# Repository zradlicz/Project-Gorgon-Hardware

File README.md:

# SDI-12 Underground Temperature Sensor

A 7-channel 4-wire RTD temperature measurement device that communicates via the SDI-12 protocol, designed for underground temperature profiling applications.

## Overview

This device is an SDI-12 sensor that provides high-precision temperature measurements from seven 4-wire RTD (Resistance Temperature Detector) inputs. It is designed for underground temperature sensing applications such as soil temperature profiling, permafrost monitoring, and geothermal studies. The 4-wire RTD configuration eliminates lead resistance errors, enabling accurate measurements even with long cable runs to buried sensors.

Built around the Raspberry Pi RP2040 microcontroller and featuring a 24-bit ADC, the sensor integrates seamlessly with existing SDI-12 data logger infrastructure.

## Features

- **7 channels** of 4-wire RTD temperature measurement
- **24-bit precision ADC** (AD7124-8) for high-resolution measurements
- **8-channel analog multiplexer** (ADG708) for RTD channel selection
- **SDI-12 protocol** compatible with standard environmental data loggers
- **RP2040 microcontroller** (dual-core Arm Cortex-M0+)
- **USB interface** for configuration and direct data access
- **128Mb flash memory** for configuration storage
- **Weatherproof enclosure** with gasket seal for field deployment

## Hardware Specifications

| Parameter | Value |
|-----------|-------|
| RTD Channels | 7 (4-wire configuration) |
| ADC Resolution | 24-bit |
| Communication | SDI-12, USB |
| Power Supply | 5V |
| Logic Level | 3.3V (internal) |
| MCU | RP2040 (Raspberry Pi) |

## Key Components

| Reference | Part | Description |
|-----------|------|-------------|
| U7 | RP2040 | Main microcontroller |
| U8 | AD7124-8BCPZ | 24-bit 8-channel ADC |
| U5 | ADG708BRUZ | 8-channel analog multiplexer |
| U4 | W25Q128JVS | 128Mb SPI flash memory |
| U3 | TXS0102DCT | Bidirectional level shifter |
| U2 | NCP1117-3.3 | 3.3V voltage regulator |
| U1 | LP2950-5.0 | 5V voltage regulator |

## Repository Structure

```
├── sdi12-analog-mux.kicad_sch    # KiCad schematic
├── sdi12-analog-mux.kicad_pcb    # KiCad PCB layout
├── sdi12-analog-mux.kicad_pro    # KiCad project file
├── sdi12-analog-mux.step         # 3D model of assembled PCB
├── CAD/
│   ├── assembly.FCStd            # FreeCAD full assembly
│   ├── bottom_housing.FCStd      # Bottom enclosure design
│   ├── PCB.FCStd                 # PCB model
│   └── enclosure/
│       ├── Bottom.stl            # 3D printable bottom housing
│       ├── Cover.stl             # 3D printable top cover
│       ├── Gasket.stl            # 3D printable gasket
│       ├── Gasket_Drawing.dxf    # Gasket cutting template
│       └── *.step                # STEP files for CAD import
└── production/
    ├── bom.csv                   # Bill of materials
    ├── positions.csv             # Component placement data
    ├── designators.csv           # Component designators
    └── netlist.ipc               # IPC netlist
```

## Applications

- Soil temperature profiling
- Permafrost and active layer monitoring
- Geothermal gradient measurement
- Agricultural soil monitoring
- Infrastructure temperature monitoring (roads, pipelines)
- Environmental research

## Manufacturing

Production files are located in the `production/` directory:
- **BOM**: `bom.csv` contains the complete bill of materials
- **Pick and Place**: `positions.csv` provides component placement coordinates
- **Gerbers**: Included in `sdi12-analog-mux.zip`

## Enclosure

The enclosure is designed for 3D printing and field deployment:
- Bottom housing with mounting features
- Top cover
- Gasket for weatherproof sealing
- Provisions for cable glands and ventilation

STL files for printing and STEP files for CAD integration are provided in `CAD/enclosure/`.

## Design Tools

- **PCB Design**: KiCad 8
- **Mechanical Design**: FreeCAD

## License

This project is open-source hardware.

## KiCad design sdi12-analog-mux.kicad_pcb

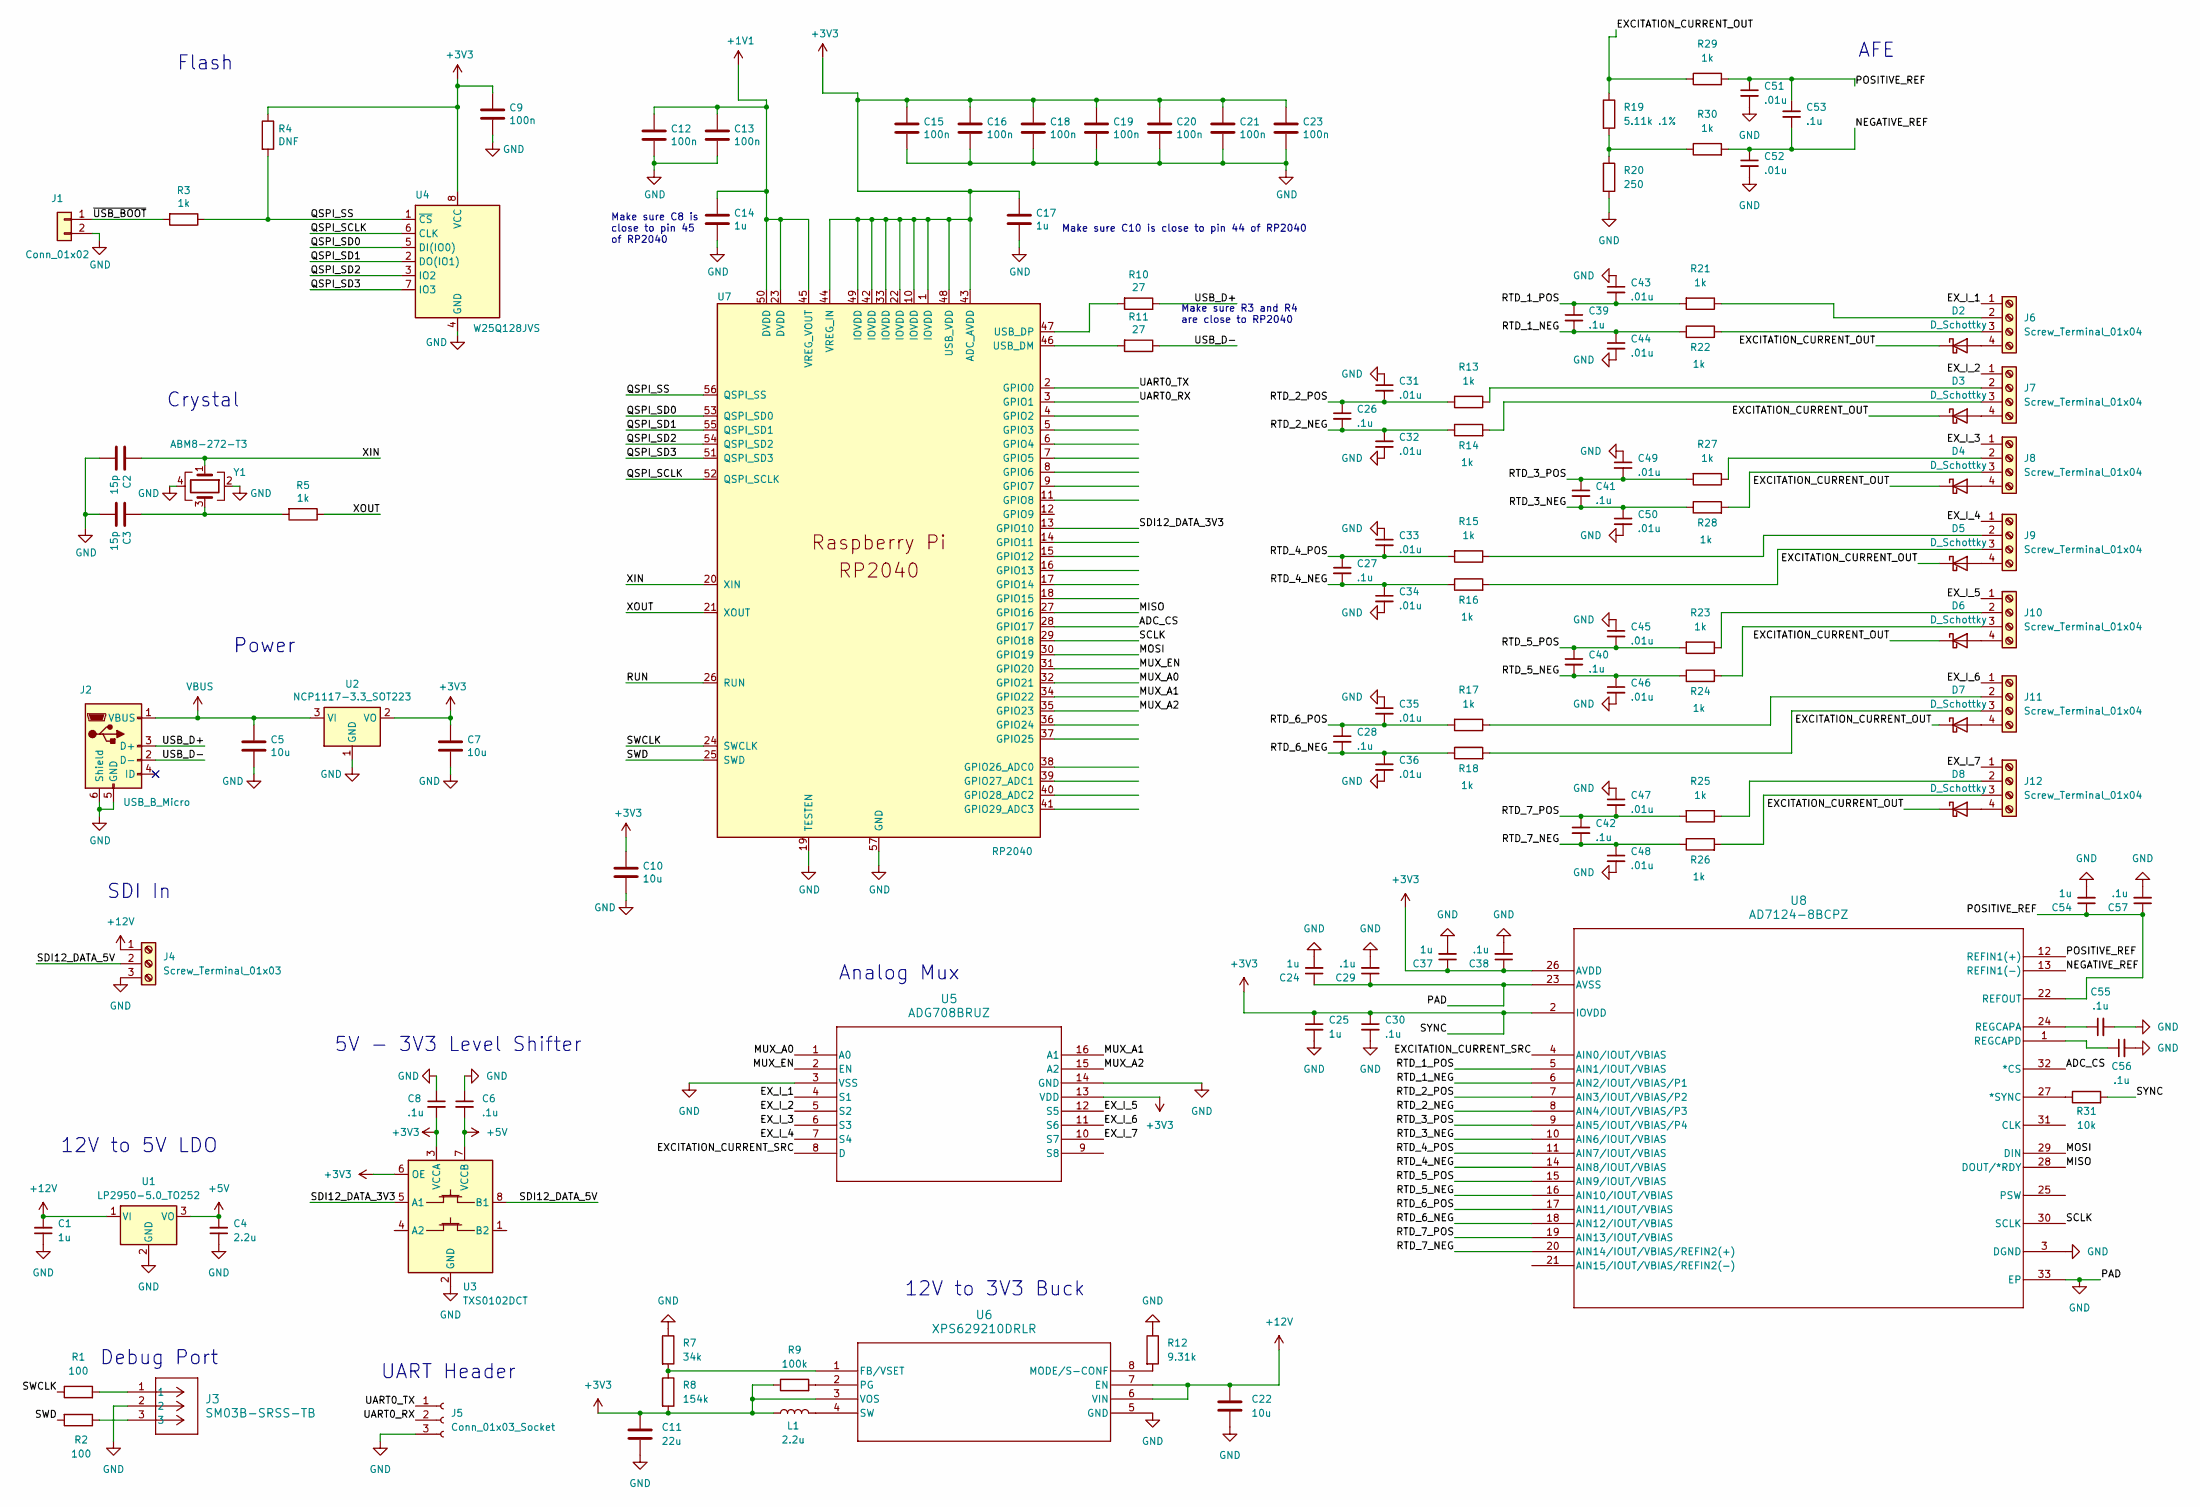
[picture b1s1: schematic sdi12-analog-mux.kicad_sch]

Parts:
C1, C24, C25, C37: 1u; C_0805_2012Metric
C2, C3: 15p; C_0402_1005Metric
C4: 2.2u; C_0402_1005Metric
C5, C7, C10: 10u; C_0805_2012Metric
C6, C8, C26, C27, C28, C29, C30, C38, C39, C40, C41, C42, C53, C55, C56, C57: .1u; C_0402_1005Metric
C9, C12, C13, C15, C16, C18, C19, C20, C21, C23: 100n; C_0402_1005Metric
C11: 22u; C_0402_1005Metric
C14, C17, C54: 1u; C_0402_1005Metric
C22: 10u; C_0402_1005Metric
C31, C32, C33, C34, C35, C36, C43, C44, C45, C46, C47, C48, C49, C50, C51, C52: .01u; C_0402_1005Metric
D2, D3, D4, D5, D6, D7, D8: D_Schottky; D_SOD-323F
J1: Conn_01x02; PinHeader_1x02_P2.54mm_Vertical
J2: USB_B_Micro; USB_Micro-B_Amphenol_10103594-0001LF_Horizontal_modified
J3: SM03B-SRSS-TB; CONN_SM03B-SRSS-TB_JST
J4: Screw_Terminal_01x03; TerminalBlock_Xinya_XY308-2.54-3P_1x03_P2.54mm_Horizontal
J5: Conn_01x03_Socket; PinHeader_1x03_P2.54mm_Vertical
J6, J7, J8, J9, J10, J11, J12: Screw_Terminal_01x04; TerminalBlock_Xinya_XY308-2.54-4P_1x04_P2.54mm_Horizontal
L1: 2.2u; WE-MAPI_3012
R1, R2: 100; R_0402_1005Metric
R3, R5, R13, R14, R15, R16, R17, R18, R21, R22, R23, R24, R25, R26, R27, R28, R29, R30: 1k; R_0402_1005Metric
R4: DNF; R_0402_1005Metric
R7: 34k; R_0402_1005Metric
R8: 154k; R_0402_1005Metric
R9: 100k; R_0402_1005Metric
R10, R11: 27; R_0402_1005Metric
R12: 9.31k; R_0402_1005Metric
R19: 5.11k .1%; R_0402_1005Metric
R20: 250; R_0402_1005Metric
R31: 10k; R_0402_1005Metric
U1: LP2950-5.0_TO252; TO-252-2
U2: NCP1117-3.3_SOT223; SOT-223-3_TabPin2
U3: TXS0102DCT; SSOP-8_2.95x2.8mm_P0.65mm
U4: W25Q128JVS; SOIC-8_5.23x5.23mm_P1.27mm
U5: ADG708BRUZ; RU_16_ADI
U6: XPS629210DRLR; SOT_9210DRLR_TEX-M
U7: RP2040; RP2040-QFN-56
U8: AD7124-8BCPZ; CP_32_12_ADI-M
Y1: ABM8-272-T3; Crystal_SMD_3225-4Pin_3.2x2.5mm

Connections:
+1V1: C12.1, C13.1, C14.1, U7.23 (DVDD), U7.45 (VREG_VOUT), U7.50 (DVDD)
+3V3: C7.1, C8.2, C9.1, C10.1, C11.1, C15.1, C16.1, C17.1, C18.1, C19.1, C20.1, C21.1, C23.1, C25.1, C30.1, C37.1, C38.1, L1.1, R4.1, R8.2, R9.1, R31.2, U2.2 (VO), U3.3 (VCCA), U3.6 (OE), U4.8 (VCC), U5.13 (VDD), U6.3 (VOS), U7.1 (IOVDD), U7.10 (IOVDD), U7.22 (IOVDD), U7.33 (IOVDD), U7.42 (IOVDD), U7.43 (ADC_AVDD), U7.44 (VREG_IN), U7.48 (USB_VDD), U7.49 (IOVDD), U8.2 (IOVDD), U8.26 (AVDD)
+5V: C4.2, C6.2, U1.3 (VO), U3.7 (VCCB)
+12V: C1.2, C22.1, J4.1, U1.1 (VI), U6.6 (VIN), U6.7 (EN)
/ADC_CS: U7.28 (GPIO17), U8.32 (*CS)
/EXCITATION_CURRENT_OUT: D2.1 (K), D3.1 (K), D4.1 (K), D5.1 (K), D6.1 (K), D7.1 (K), D8.1 (K), R19.1, R29.1
/EXCITATION_CURRENT_SRC: U5.8 (D), U8.4 (AIN0/IOUT/VBIAS)
/EX_I_1: J6.1, U5.4 (S1)
/EX_I_2: J7.1, U5.5 (S2)
/EX_I_3: J8.1, U5.6 (S3)
/EX_I_4: J9.1, U5.7 (S4)
/EX_I_5: J10.1, U5.12 (S5)
/EX_I_6: J11.1, U5.11 (S6)
/EX_I_7: J12.1, U5.10 (S7)
/MISO: U7.27 (GPIO16), U8.28 (DOUT/*RDY)
/MOSI: U7.30 (GPIO19), U8.29 (DIN)
/MUX_A0: U5.1 (A0), U7.32 (GPIO21)
/MUX_A1: U5.16 (A1), U7.34 (GPIO22)
/MUX_A2: U5.15 (A2), U7.35 (GPIO23)
/MUX_EN: U5.2 (EN), U7.31 (GPIO20)
/NEGATIVE_REF: C52.1, C53.2, R30.2, U8.13 (REFIN1(-))
/POSITIVE_REF: C51.1, C53.1, C54.1, C57.1, R29.2, U8.12 (REFIN1(+)), U8.22 (REFOUT)
/QSPI_SCLK: U4.6 (CLK), U7.52 (QSPI_SCLK)
/QSPI_SD0: U4.5 (DI(IO0)), U7.53 (QSPI_SD0)
/QSPI_SD1: U4.2 (DO(IO1)), U7.55 (QSPI_SD1)
/QSPI_SD2: U4.3 (IO2), U7.54 (QSPI_SD2)
/QSPI_SD3: U4.7 (IO3), U7.51 (QSPI_SD3)
/QSPI_SS: R3.1, R4.2, U4.1 (~CS), U7.56 (QSPI_SS)
/RTD_1_NEG: C39.2, C44.1, R22.1, U8.6 (AIN2/IOUT/VBIAS/P1)
/RTD_1_POS: C39.1, C43.2, R21.2, U8.5 (AIN1/IOUT/VBIAS)
/RTD_2_NEG: C26.2, C32.1, R14.1, U8.8 (AIN4/IOUT/VBIAS/P3)
/RTD_2_POS: C26.1, C31.2, R13.2, U8.7 (AIN3/IOUT/VBIAS/P2)
/RTD_3_NEG: C41.2, C50.1, R28.1, U8.10 (AIN6/IOUT/VBIAS)
/RTD_3_POS: C41.1, C49.2, R27.2, U8.9 (AIN5/IOUT/VBIAS/P4)
/RTD_4_NEG: C27.2, C34.1, R16.1, U8.14 (AIN8/IOUT/VBIAS)
/RTD_4_POS: C27.1, C33.2, R15.2, U8.11 (AIN7/IOUT/VBIAS)
/RTD_5_NEG: C40.2, C46.1, R24.1, U8.16 (AIN10/IOUT/VBIAS)
/RTD_5_POS: C40.1, C45.2, R23.2, U8.15 (AIN9/IOUT/VBIAS)
/RTD_6_NEG: C28.2, C36.1, R18.1, U8.18 (AIN12/IOUT/VBIAS)
/RTD_6_POS: C28.1, C35.2, R17.2, U8.17 (AIN11/IOUT/VBIAS)
/RTD_7_NEG: C42.2, C48.1, R26.1, U8.20 (AIN14/IOUT/VBIAS/REFIN2(+))
/RTD_7_POS: C42.1, C47.2, R25.2, U8.19 (AIN13/IOUT/VBIAS)
/RUN: U7.26 (RUN)
/SCLK: U7.29 (GPIO18), U8.30 (SCLK)
/SDI12_DATA_3V3: U3.5 (A1), U7.13 (GPIO10)
/SDI12_DATA_5V: J4.2, U3.8 (B1)
/SWCLK: R1.1, U7.24 (SWCLK)
/SWD: R2.2, U7.25 (SWD)
/UART0_RX: J5.2, U7.3 (GPIO1)
/UART0_TX: J5.1, U7.2 (GPIO0)
/USB_D+: J2.3 (D+), R10.1
/USB_D-: J2.2 (D-), R11.1
/XIN: C2.1, U7.20 (XIN), Y1.1
/XOUT: R5.1, U7.21 (XOUT)
/~USB_BOOT: J1.1, R3.2
GND: C1.1, C2.2, C3.2, C4.1, C5.2, C6.1, C7.2, C8.1, C9.2, C10.2, C11.2, C12.2, C13.2, C14.2, C15.2, C16.2, C17.2, C18.2, C19.2, C20.2, C21.2, C22.2, C23.2, C24.1, C24.2, C25.2, C29.1, C29.2, C30.2, C31.1, C32.2, C33.1, C34.2, C35.1, C36.2, C37.2, C38.2, C43.1, C44.2, C45.1, C46.2, C47.1, C48.2, C49.1, C50.2, C51.2, C52.2, C54.2, C55.2, C56.2, C57.2, J1.2, J2.5 (GND), J2.6 (Shield), J3.2, J4.3, J5.3, R7.1, R12.1, R20.2, U1.2 (GND), U2.1 (GND), U3.2 (GND), U4.4 (GND), U5.3 (VSS), U5.14 (GND), U6.5 (GND), U7.19 (TESTEN), U7.57 (GND), U8.3 (DGND), U8.23 (AVSS), U8.33 (EP), Y1.2, Y1.4
unnamed: C3.1, R5.2, Y1.3
unnamed: D2.2 (A), J6.4
unnamed: D3.2 (A), J7.4
unnamed: D4.2 (A), J8.4
unnamed: D5.2 (A), J9.4
unnamed: D6.2 (A), J10.4
unnamed: D7.2 (A), J11.4
unnamed: D8.2 (A), J12.4
unnamed: J3.1, R1.2
unnamed: J3.3, R2.1
unnamed: J6.2, R21.1
unnamed: J6.3, R22.2
unnamed: J7.2, R13.1
unnamed: J7.3, R14.2
unnamed: J8.2, R27.1
unnamed: J8.3, R28.2
unnamed: J9.2, R15.1
unnamed: J9.3, R16.2
unnamed: J10.2, R23.1
unnamed: J10.3, R24.2
unnamed: J11.2, R17.1
unnamed: J11.3, R18.2
unnamed: J12.2, R25.1
unnamed: J12.3, R26.2
unnamed: R19.2, R20.1, R30.1
unnamed: R7.2, R8.1, U6.1 (FB/VSET)
unnamed: R12.2, U6.8 (MODE/S-CONF)
unnamed: R9.2, U6.2 (PG)
unnamed: L1.2, U6.4 (SW)
unnamed: R11.2, U7.46 (USB_DM)
unnamed: R10.2, U7.47 (USB_DP)
unnamed: R31.1, U8.27 (*SYNC)
unnamed: C55.1, U8.24 (REGCAPA)
unnamed: C56.1, U8.1 (REGCAPD)
VBUS: C5.1, J2.1 (VBUS), U2.3 (VI)

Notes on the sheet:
UART Header
Power
12V to 3V3 Buck
Debug Port
5V - 3V3 Level Shifter
Crystal
Analog Mux
Flash
Make sure R3 and R4 are close to RP2040
Make sure C10 is close to pin 44 of RP2040
12V to 5V LDO
Make sure C8 is close to pin 45 of RP2040
SDI In
AFE

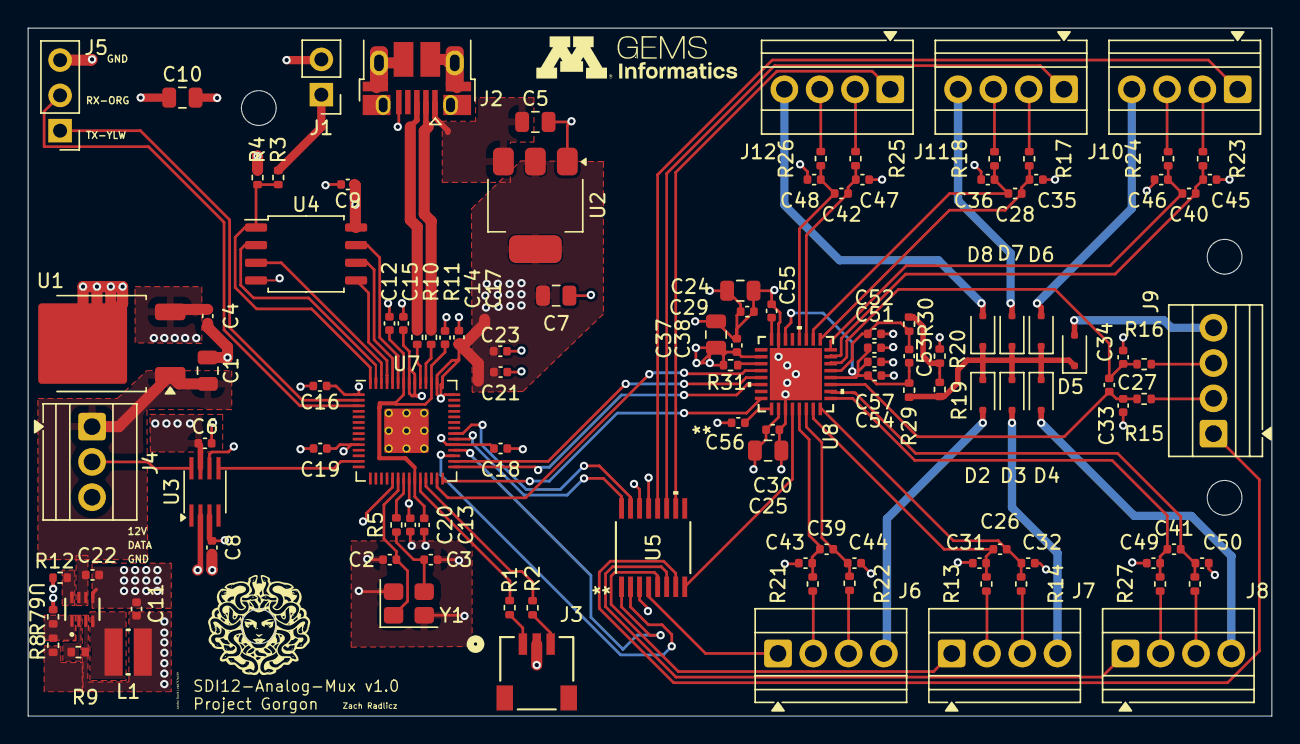
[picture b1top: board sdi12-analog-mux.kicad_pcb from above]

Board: 4 copper layers, 89.5 x 49.5 mm, 118 parts (0 on the bottom side), 90 nets.

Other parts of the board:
a: LOGO
a#2: LOGO

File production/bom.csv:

Designator,Footprint,Quantity,Value,LCSC Part #
"C1, C24, C25, C37",0805,4,1u,
"C10, C5, C7",0805,3,10u,
C11,0402,1,22u,
"C12, C13, C15, C16, C18, C19, C20, C21, C23, C9",0402,10,100n,
"C14, C17, C54",0402,3,1u,
"C2, C3",0402,2,15p,
C22,0402,1,10u,
"C26, C27, C28, C29, C30, C38, C39, C40, C41, C42, C53, C55, C56, C57, C6, C8",0402,16,.1u,
"C31, C32, C33, C34, C35, C36, C43, C44, C45, C46, C47, C48, C49, C50, C51, C52",0402,16,.01u,
C4,0402,1,2.2u,
"D2, D3, D4, D5, D6, D7, D8",D_SOD-323F,7,D_Schottky,
J1,PinHeader_1x02_P2.54mm_Vertical,1,Conn_01x02,
"J10, J11, J12, J6, J7, J8, J9",TerminalBlock_Xinya_XY308-2.54-4P_1x04_P2.54mm_Horizontal,7,Screw_Terminal_01x04,
J2,USB_Micro-B_Amphenol_10103594-0001LF_Horizontal_modified,1,USB_B_Micro,
J3,CONN_SM03B-SRSS-TB_JST,1,SM03B-SRSS-TB,
J4,TerminalBlock_Xinya_XY308-2.54-3P_1x03_P2.54mm_Horizontal,1,Screw_Terminal_01x03,
J5,PinHeader_1x03_P2.54mm_Vertical,1,Conn_01x03_Socket,
L1,WE-MAPI_3012,1,2.2u,
"R1, R2",0402,2,100,
"R10, R11",0402,2,27,
R12,0402,1,9.31k,
"R13, R14, R15, R16, R17, R18, R21, R22, R23, R24, R25, R26, R27, R28, R29, R3, R30, R5",0402,18,1k,
R19,0402,1,5.11k .1%,
R20,0402,1,250,
R31,0402,1,10k,
R4,0402,1,DNF,
R7,0402,1,34k,
R8,0402,1,154k,
R9,0402,1,100k,
U1,TO-252-2,1,LP2950-5.0_TO252,
U2,SOT-223-3_TabPin2,1,NCP1117-3.3_SOT223,
U3,SSOP-8_2.95x2.8mm_P0.65mm,1,TXS0102DCT,
U4,SOIC-8_5.23x5.23mm_P1.27mm,1,W25Q128JVS,
U5,RU_16_ADI,1,ADG708BRUZ,
U6,SOT_9210DRLR_TEX-M,1,XPS629210DRLR,
U7,RP2040-QFN-56,1,RP2040,
U8,CP_32_12_ADI-M,1,AD7124-8BCPZ,
Y1,Crystal_SMD_3225-4Pin_3.2x2.5mm,1,ABM8-272-T3,

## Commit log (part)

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2025-10-10 initial commit with somewhat routed 2 layer board
2025-10-17 ordered boards v0.0 and started CAD
2025-10-31 updated before major changes
2025-11-05 version 1.0 after v0.0 bringup modifications
2026-01-15 added encolsure files
2026-01-20 added STLs for updated enclosure
2026-01-26 Added Gasket dxf file
2026-01-29 added readme
